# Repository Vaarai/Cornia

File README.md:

<h1 align="center">
 
</h1>

# Cornia keyboard

<h1 align="center">
 
</h1>

The Cornia keyboard is a split keyboard featuring : 
* 3x6 column strongly staggered keys and 3 thumb keys
* Hotswap sockets (Compatible with Kailh and Gateron)
* All 1u keys
* Same PCB for both hands (revesible)
* No diode to solder (No switch matrix)
* Per key adressable RGB leds (SK6812MINI-E)
* QMK Handedness pin (see [QMK documentation](https://github.com/qmk/qmk_firmware/blob/master/docs/config_options.md#setting-handedness))

### Why this name ?

Because it was inspired from the [Corne](https://github.com/foostan/crkbd/tree/main) keyboard, and `Cornia` came in mind.

### Table of contents

<!--ts-->
  * [Quick steps](#quick-steps)
  * [Hardware](#hardware)
    * [Bill of material](#bill-of-material)
    * [Compatible controllers](#compatible-controllers)
    * [PCB Design](#pcb-design-and-manufacturing)
    * [Keyboard assembling](#keyboard-assembling)
    * [Troubleshooting](#troubleshooting)
  * [Software](#software)
    * [Cornia not yet integrated in official QMK ?](#cornia-not-yet-integrated-in-official-qmk)
    * [Keymap](#keymap)
  * [Case](#case)
  * [Photos](#photos)
<!--te-->

# Quick steps

1. [Order the PCB](./doc/pcb_ordering.md)
2. [Print the case](https://www.printables.com/model/958200-case-for-cornia-v1-including-a-trackpad-version-40)
3. [Assemble/solder PCB](./doc/assembly_guide.md)
4. [Flash Cornia QMK](https://github.com/Vaarai/qmk_firmware/tree/cornia/keyboards/cornia)

# Hardware

### Bill of material

| Name | Count | Remarks |
|:-|:-|:-|
| PCB | 2 | [PCB Ordering guide](./doc/pcb_ordering.md) |
| OLED Display | 2 | |
| [RP2040 ProMicro](https://keeb.io/products/rp2040-pro-micro-usb-c-controller) | 2 | Alternative: Refer to [Compatible controllers](#compatible-controllers) |
| TRRS 3.5mm jack | 2 | Ref: PJ-320A |
| Reset switch | 2 | SMD 4x4mm |
| I²C Pull-up resistors | 2 | 0805 form-factor and any value between 2.2kΩ and 4.7kΩ |
| Handedness Pull-up/down resistor | 1 | 0805 form-factor and any value between 2.2kΩ and 4.7kΩ |
| Hotswap sockets | 42 | Compatible with Kailh and Gateron |
| Key switches | 42 | Only compatible with MX style |
| Keycaps | 42 | 1u size |
| TRRS (4 poles) cable | 1 | |
| USB cable | 1 | USB Micro or USB-C depending on the controller, avoid charge-only cables |
| Case | 2 | [Cornia v1 Printables](https://www.printables.com/model/958200-case-for-cornia-v1-including-a-trackpad-version-40) |

### Compatible controllers

| Reference | I²C OLED Display | Handedness pin | Other features |
|:-|:-:|:-:|:-:|
| [RP2040 Aliexpress](https://fr.aliexpress.com/item/1005005980167753.html) | $${\color{green}✓}$$ | $${\color{green}✓}$$ | $${\color{green}✓}$$ |
| [RP2040 keeb.io](https://keeb.io/products/rp2040-pro-micro-usb-c-controller) | $${\color{green}✓}$$ | $${\color{green}✓}$$ | $${\color{green}✓}$$ |
| [0xCB-Helios](https://github.com/0xCB-dev/0xCB-Helios) | $${\color{green}✓}$$ | $${\color{green}✓}$$ | $${\color{green}✓}$$ |
| [Elite-Pi](https://docs.keeb.io/elite-pi-guide) | $${\color{red}⨯}$$ | $${\color{red}⨯}$$ | $${\color{green}✓}$$ |
| [RP Micro](https://github.com/siderakb/rp-micro) | $${\color{red}⨯}$$ | $${\color{red}⨯}$$ | $${\color{green}✓}$$ |

### PCB design and manufacturing

Schematic and PCB views are available in `pdf/`:
- [Schematic](pdf/SCH.pdf)
- [PCB Top view](pdf/PCB_TOP.pdf)
- [PCB Bottom view](pdf/PCB_BOT.pdf)

To manufacture the Cornia PCB please follow the [PCB manufacturing guide](./doc/pcb_ordering.md)

In case you want to modify the PCB please take a look at the following:
- KiCad [project description](./PCB/README.md)
- Export bash script to ease the process, it is documented in [Manufacturing files export guide](./doc/manufacturing_files_export.md)

### Keyboard assembling

To solder and assemble the Cornia keyboard please follow the [Cornia assembly guide](./doc/assembly_guide.md)

### Troubleshooting

[Troubleshooting guide](./doc/troubleshooting_pcb.md)

# Software

Cornia keyboard firmware is based on QMK.

### Cornia not yet integrated in official QMK ?

If Cornia keyboard not yet integrated in [qmk_firmware](https://github.com/qmk/qmk_firmware) you can go to [Vaarai QMK fork](https://github.com/Vaarai/qmk_firmware/tree/cornia/keyboards/cornia) on and follow the readme.

### Keymap

- [Default QWERTY layout for Cornia keyboard](https://www.keyboard-layout-editor.com/#/gists/5af136790cefe4b35cdf02ca52c1fccc)
- [Fire layout for Cornia keyboard](https://www.keyboard-layout-editor.com/#/gists/a40345c92e1f3f326426ef890ebf4d1c) (Based on [Fire (Oxey)](https://bit.ly/layout-doc-v2) layout)

# Case

Case for Cornia v1 is available on [Cornia v1 Printables](https://www.printables.com/model/958200-case-for-cornia-v1-including-a-trackpad-version-40) from user Rikiki, optionally including a trackpad version (40mm) available for both halves.

Cornia keyboard is a project initiated by a post from `help-forum` on [QMK Discord](https://discord.gg/qmk).

User Rikiki requested in this post if someone could alter [crkbd](https://github.com/foostan/crkbd) PCB to match his requirements.

I (Vaarai) replied to this post and in 1 months we made 2 iterations of crkbd variant and it diverged from crkbd in a way that we started to make a new keyboard and 5 months later it lead to the Cornia.

Rikiki made all the mechanical parts and I designed the PCB then developed a QMK implementation.

# Photos

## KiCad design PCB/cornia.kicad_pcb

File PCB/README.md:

# Cornia KiCad project overview

This KiCad project is designed for the Cornia keyboard PCB

## KiCad files Descriptions

- __cornia.kicad_pro:__ This is the main project file for KiCad. It contains general information about the project, such as library paths, and links to schematic and PCB files.
- __cornia.sch:__ This file defines the circuit diagram and component connections.
- __cornia.kicad_pcb:__ This file contains the PCB layout, including component placement, routing, and layer definitions.
- __cornia.kicad_sym:__ This file defines the symbol for a custom component used in the schematics.
- __cornia.kicad_mod:__ This file defines the footprint for a custom component used in the PCB layout.
- __cornia.pdf:__ This file contains any relevant documentation or information about the project.

## Usage
- __Open the project:__ Launch KiCad and open __cornia.kicad_pro__ file.
- __View schematics:__ Open schematic file from the project view.
- __Inspect PCB layout:__ Open PCB layout file from the project view.
- __Modify as needed:__ Make any necessary changes to the schematics and/or PCB layout.
- __Generate Gerber files:__ If you're ready to manufacture the PCB, generate the Gerber files from the PCB layout.

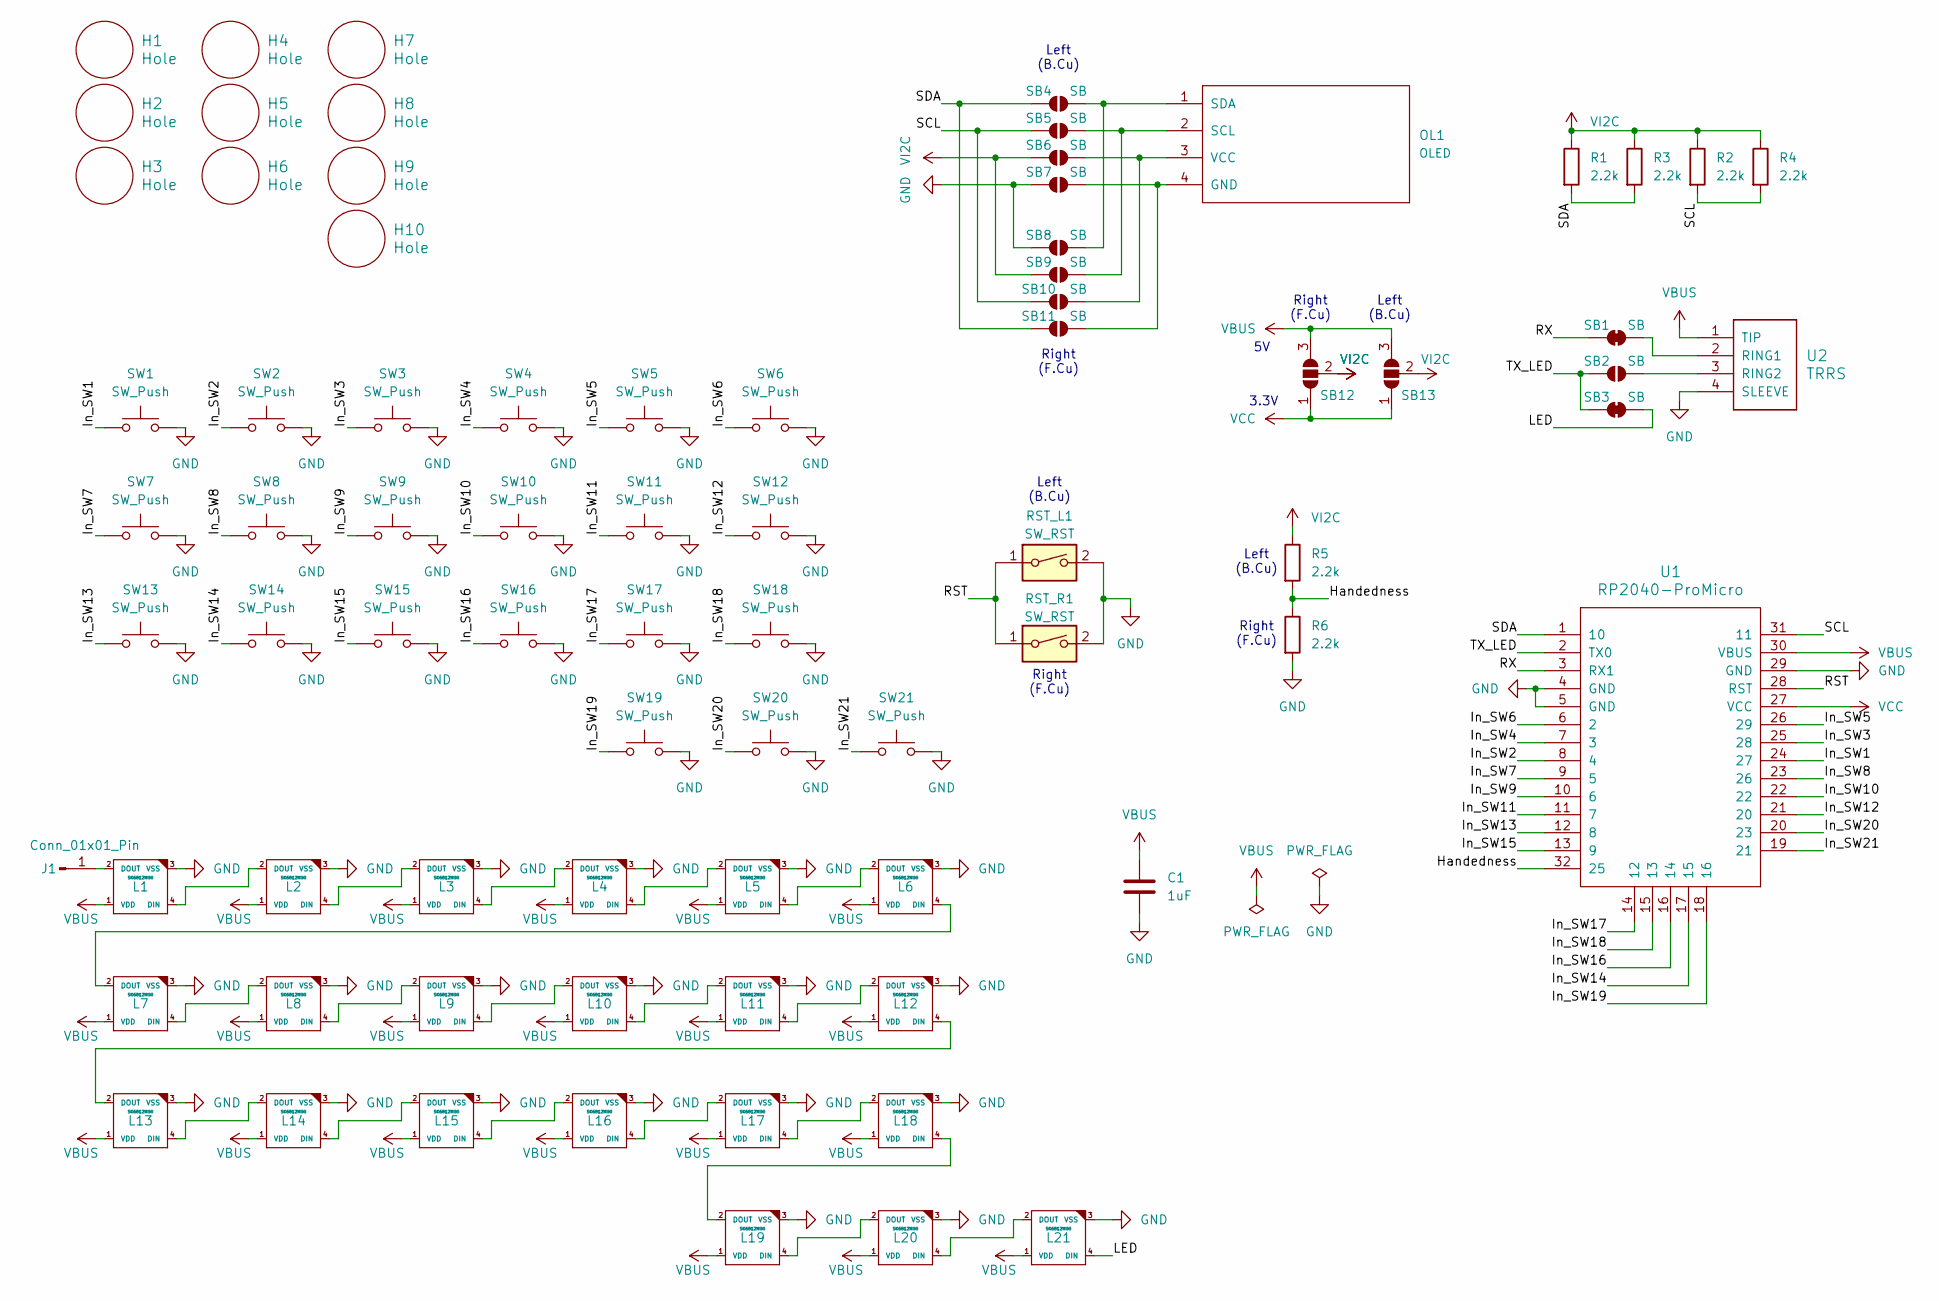
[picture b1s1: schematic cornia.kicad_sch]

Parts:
C1: 1uF; C_0805
H1, H2, H3, H4, H5, H6, H7, H8, H9, H10: Hole; MountingHole_2.2mm_M2_no_annular
J1: Conn_01x01_Pin; 1Pin
L1, L2, L3, L4, L5, L6, L7, L8, L9, L10, L11, L12, L13, L14, L15, L16, L17, L18, L19, L20, L21: SK6812MINI; YS-SK6812MINI-E
OL1: OLED
R1, R2, R3, R4, R5, R6: 2.2k; R_0805
RST_L1: SW_RST; SW_SMD_4x4mm
RST_R1: SW_RST; SW_SMD_4x4mm
SB1, SB3: SB; SolderJumper-2_Bridged
SB2: SB; SolderJumper-2_Open
SB4, SB5, SB6, SB7, SB8, SB9, SB10, SB11: SB; SolderJumper-2_Open_NoSilk
SB12, SB13: SolderJumper_3_Open; SolderJumper-3_I2C
SW1, SW2, SW3, SW4, SW5, SW6, SW7, SW8, SW9, SW10, SW11, SW12, SW13, SW14, SW15, SW16, SW17, SW18, SW19, SW20, SW21: SW_Push; keyswitch_cherrymx_hotswap_reversible_1u
U1: RP2040-ProMicro
U2: TRRS; TRRS_PJ-320A

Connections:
/Handedness: R5.2, R6.1, U1.32 (25)
/In_SW1: SW1.1, U1.24 (27)
/In_SW2: SW2.1, U1.8 (4)
/In_SW3: SW3.1, U1.25 (28)
/In_SW4: SW4.1, U1.7 (3)
/In_SW5: SW5.1, U1.26 (29)
/In_SW6: SW6.1, U1.6 (2)
/In_SW7: SW7.1, U1.9 (5)
/In_SW8: SW8.1, U1.23 (26)
/In_SW9: SW9.1, U1.10 (6)
/In_SW10: SW10.1, U1.22
/In_SW11: SW11.1, U1.11 (7)
/In_SW12: SW12.1, U1.21 (20)
/In_SW13: SW13.1, U1.12 (8)
/In_SW14: SW14.1, U1.17 (15)
/In_SW15: SW15.1, U1.13 (9)
/In_SW16: SW16.1, U1.16 (14)
/In_SW17: SW17.1, U1.14 (12)
/In_SW18: SW18.1, U1.15 (13)
/In_SW19: SW19.1, U1.18 (16)
/In_SW20: SW20.1, U1.20 (23)
/In_SW21: SW21.1, U1.19 (21)
/LED: L21.4 (DIN), SB3.2 (B)
/RST: RST_L1.1, RST_R1.1, U1.28 (RST)
/RX: SB1.1 (A), U1.3 (RX1)
/SCL: R2.2, R4.2, SB5.1 (A), SB10.1 (A), U1.31 (11)
/SDA: R1.2, R3.2, SB4.1 (A), SB11.1 (A), U1.1 (10)
/TX_LED: SB2.1 (A), SB3.1 (A), U1.2 (TX0)
GND: C1.2, L1.3 (VSS), L2.3 (VSS), L3.3 (VSS), L4.3 (VSS), L5.3 (VSS), L6.3 (VSS), L7.3 (VSS), L8.3 (VSS), L9.3 (VSS), L10.3 (VSS), L11.3 (VSS), L12.3 (VSS), L13.3 (VSS), L14.3 (VSS), L15.3 (VSS), L16.3 (VSS), L17.3 (VSS), L18.3 (VSS), L19.3 (VSS), L20.3 (VSS), L21.3 (VSS), R6.2, RST_L1.2, RST_R1.2, SB7.1 (A), SB8.1 (A), SW1.2, SW2.2, SW3.2, SW4.2, SW5.2, SW6.2, SW7.2, SW8.2, SW9.2, SW10.2, SW11.2, SW12.2, SW13.2, SW14.2, SW15.2, SW16.2, SW17.2, SW18.2, SW19.2, SW20.2, SW21.2, U1.4 (GND), U1.5 (GND), U1.29 (GND), U2.4 (SLEEVE)
unnamed: J1.1, L1.2 (DOUT)
unnamed: L1.4 (DIN), L2.2 (DOUT)
unnamed: L2.4 (DIN), L3.2 (DOUT)
unnamed: L3.4 (DIN), L4.2 (DOUT)
unnamed: L4.4 (DIN), L5.2 (DOUT)
unnamed: L5.4 (DIN), L6.2 (DOUT)
unnamed: L6.4 (DIN), L7.2 (DOUT)
unnamed: L7.4 (DIN), L8.2 (DOUT)
unnamed: L8.4 (DIN), L9.2 (DOUT)
unnamed: L10.4 (DIN), L11.2 (DOUT)
unnamed: L9.4 (DIN), L10.2 (DOUT)
unnamed: L11.4 (DIN), L12.2 (DOUT)
unnamed: L12.4 (DIN), L13.2 (DOUT)
unnamed: L13.4 (DIN), L14.2 (DOUT)
unnamed: L14.4 (DIN), L15.2 (DOUT)
unnamed: L15.4 (DIN), L16.2 (DOUT)
unnamed: L16.4 (DIN), L17.2 (DOUT)
unnamed: L17.4 (DIN), L18.2 (DOUT)
unnamed: L18.4 (DIN), L19.2 (DOUT)
unnamed: L19.4 (DIN), L20.2 (DOUT)
unnamed: L20.4 (DIN), L21.2 (DOUT)
unnamed: OL1.4 (GND), SB7.2 (B), SB11.2 (B)
unnamed: OL1.2 (SCL), SB5.2 (B), SB9.2 (B)
unnamed: OL1.1 (SDA), SB4.2 (B), SB8.2 (B)
unnamed: OL1.3 (VCC), SB6.2 (B), SB10.2 (B)
unnamed: SB1.2 (B), U2.2 (RING1)
unnamed: SB2.2 (B), U2.3 (RING2)
VBUS: C1.1, L1.1 (VDD), L2.1 (VDD), L3.1 (VDD), L4.1 (VDD), L5.1 (VDD), L6.1 (VDD), L7.1 (VDD), L8.1 (VDD), L9.1 (VDD), L10.1 (VDD), L11.1 (VDD), L12.1 (VDD), L13.1 (VDD), L14.1 (VDD), L15.1 (VDD), L16.1 (VDD), L17.1 (VDD), L18.1 (VDD), L19.1 (VDD), L20.1 (VDD), L21.1 (VDD), SB12.3 (B), SB13.3 (B), U1.30 (VBUS), U2.1 (TIP)
VCC: SB12.1 (A), SB13.1 (A), U1.27 (VCC)
VI2C: R1.1, R2.1, R3.1, R4.1, R5.1, SB6.1 (A), SB9.1 (A), SB12.2 (C), SB13.2 (C)

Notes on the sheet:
Right (F.Cu)
Left (B.Cu)
3.3V

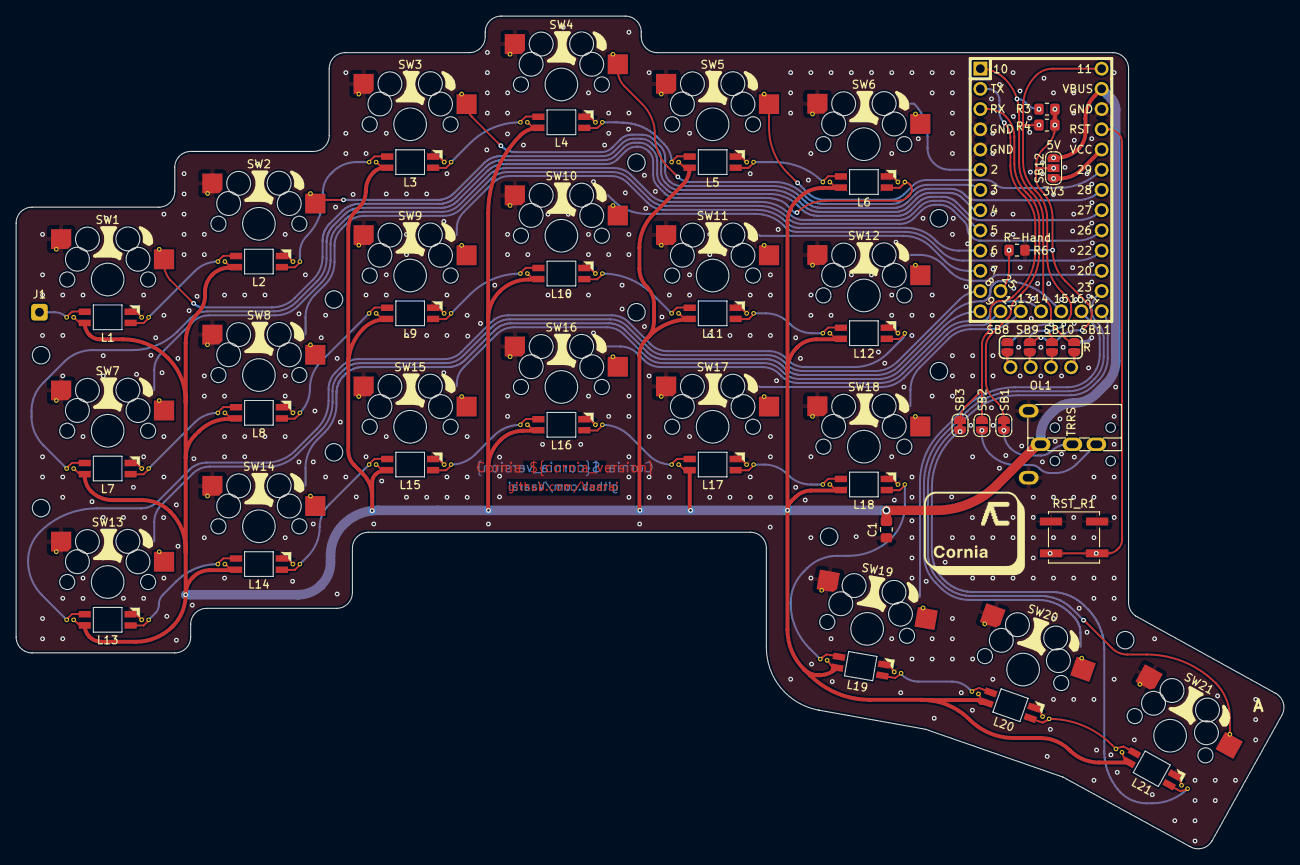
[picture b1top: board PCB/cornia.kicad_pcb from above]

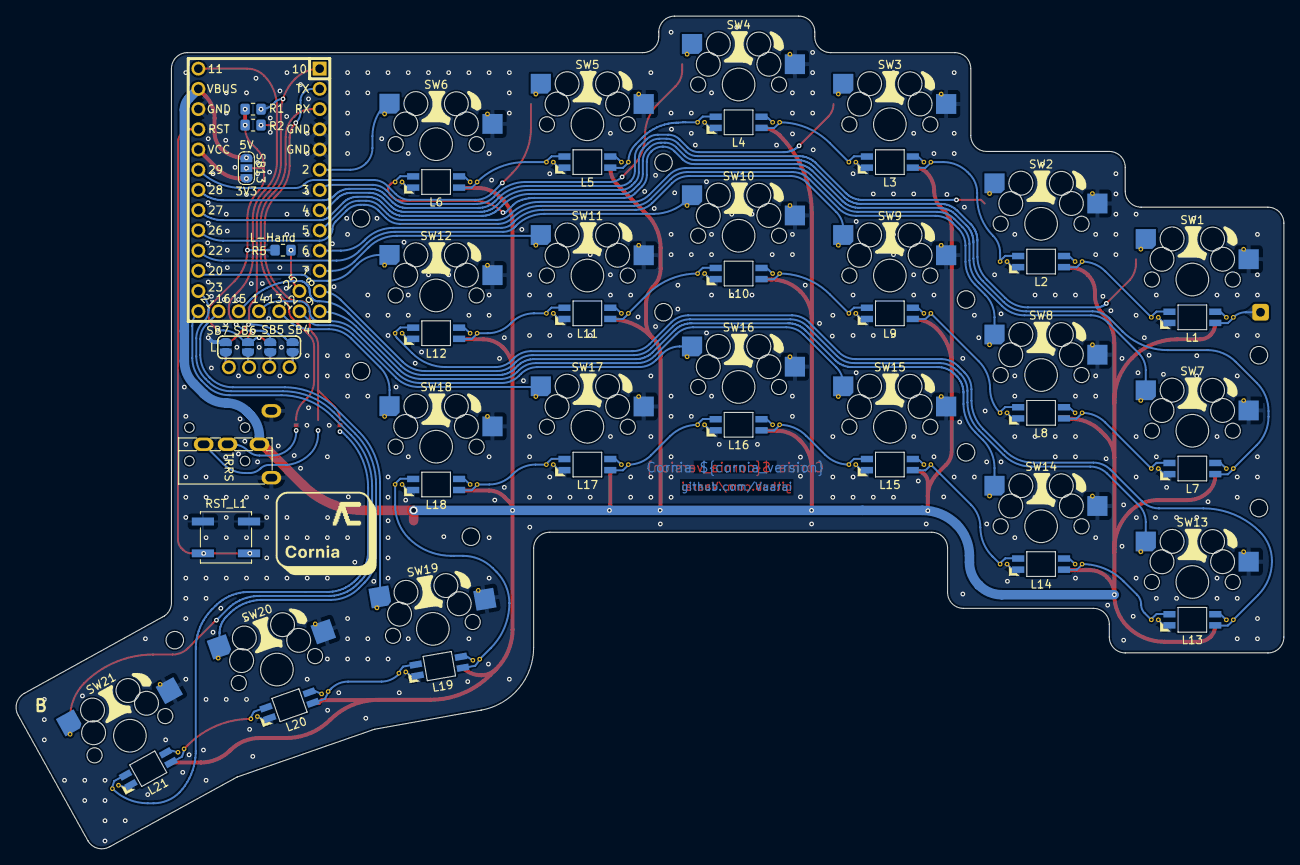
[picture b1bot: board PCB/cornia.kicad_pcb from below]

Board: 2 copper layers, 159.3 x 104.6 mm, 78 parts (9 on the bottom side), 59 nets.

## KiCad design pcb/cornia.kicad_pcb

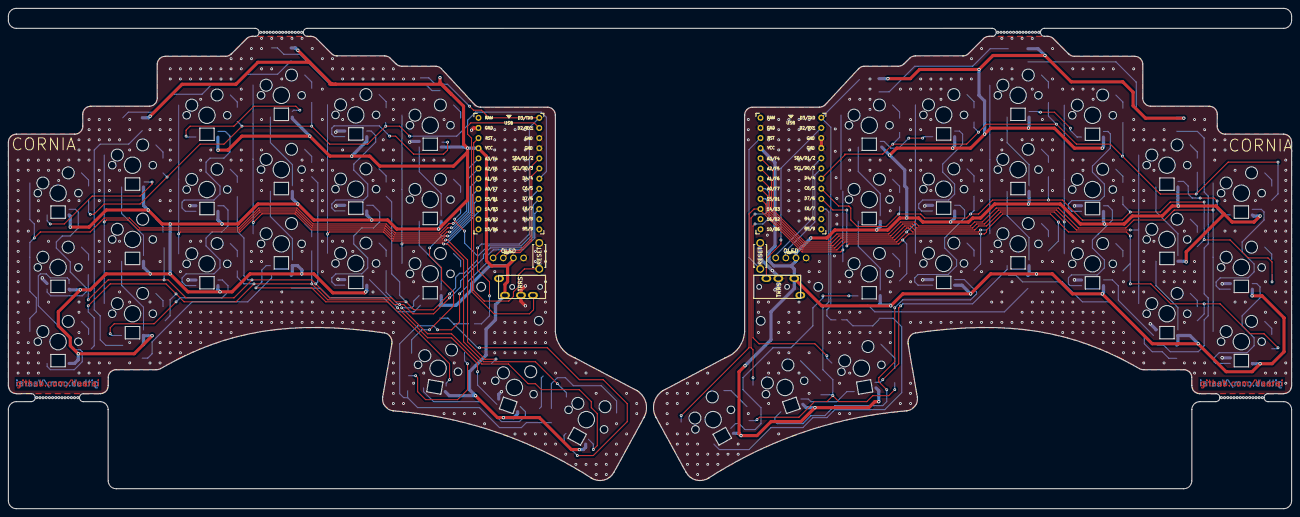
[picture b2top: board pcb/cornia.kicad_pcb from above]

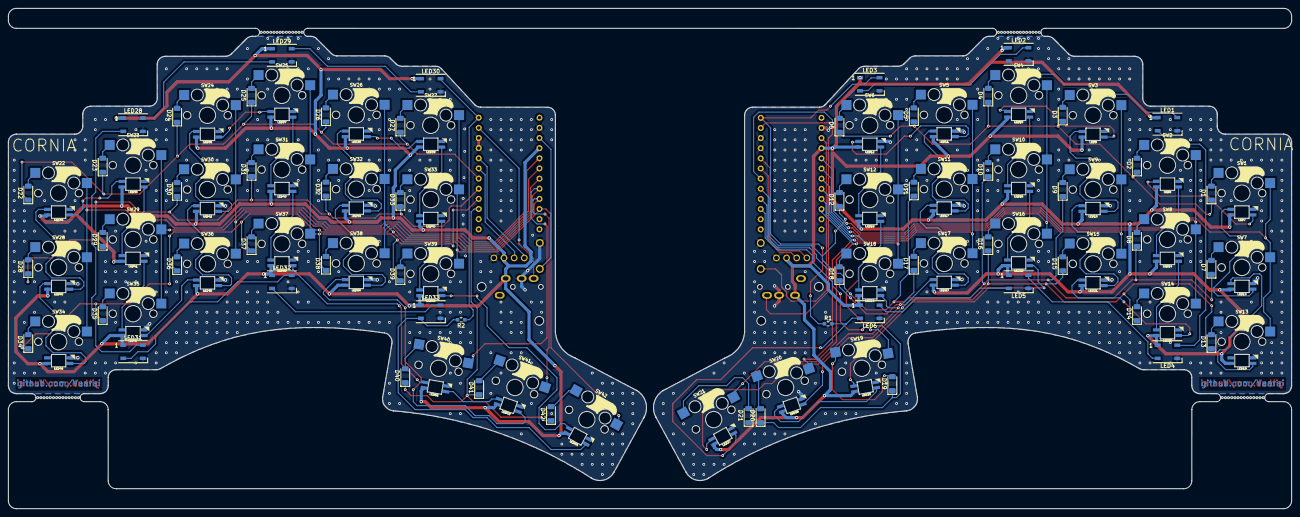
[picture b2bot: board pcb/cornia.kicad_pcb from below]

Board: 2 copper layers, 321.4 x 125.3 mm, 152 parts (142 on the bottom side), 128 nets.

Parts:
D1, D2, D3, D4, D5, D6, D7, D8, D9, D10, D11, D12, D13, D14, D15, D16, D17, D18, D19, D20, D21, D22, D23, D24, D25, D26, D27, D28, D29, D30, D31, D32, D33, D34, D35, D36, D37, D38, D39, D40, D41, D42: D; D_MiniMELF
J1, J3: MJ-4PP-9
J2, J4: OLED
LED1, LED2, LED3, LED4, LED5, LED6, LED28, LED29, LED30, LED31, LED32, LED33: WS2812B; LED_WS2812B_PLCC4_5.0x5.0mm_P3.2mm
LED7, LED8, LED9, LED10, LED11, LED12, LED13, LED14, LED15, LED16, LED17, LED18, LED19, LED20, LED21, LED22, LED23, LED24, LED25, LED26, LED27, LED34, LED35, LED36, LED37, LED38, LED39, LED40, LED41, LED42, LED43, LED44, LED45, LED46, LED47, LED48, LED49, LED50, LED51, LED52, LED53, LED54: YS-SK6812MINI-E
R1, R2: 0; R_0603_1608Metric_Pad0.98x0.95mm_HandSolder
RSW1, RSW2: SW_PUSH; ResetSW
Ref**: Val**; MountingHole_2.2mm_M2_ISO7380
Ref**#2, Ref**#3, Ref**#4: Val**; MountingHole_2.2mm_M2_ISO7380
SW1, SW2, SW3, SW4, SW5, SW6, SW7, SW8, SW9, SW10, SW11, SW12, SW13, SW14, SW15, SW16, SW17, SW18, SW19, SW20, SW21, SW22, SW23, SW24, SW25, SW26, SW27, SW28, SW29, SW30, SW31, SW32, SW33, SW34, SW35, SW36, SW37, SW38, SW39, SW40, SW41, SW42: SW_PUSH; keyswitch_cherrymx_hotswap_1u
U1, U2: ProMicro

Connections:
GND: J1.C, J2.4, LED1.3 (VSS), LED2.3 (VSS), LED3.3 (VSS), LED4.3 (VSS), LED5.3 (VSS), LED6.3 (VSS), LED7.3 (VSS), LED8.3 (VSS), LED9.3 (VSS), LED10.3 (VSS), LED11.3 (VSS), LED12.3 (VSS), LED13.3 (VSS), LED14.3 (VSS), LED15.3 (VSS), LED16.3 (VSS), LED17.3 (VSS), LED18.3 (VSS), LED19.3 (VSS), LED20.3 (VSS), LED21.3 (VSS), LED22.3 (VSS), LED23.3 (VSS), LED24.3 (VSS), LED25.3 (VSS), LED26.3 (VSS), LED27.3 (VSS), RSW1.2, U1.3 (GND), U1.4 (GND), U1.23 (GND)
GNDA: J3.C, J4.4, LED28.3 (VSS), LED29.3 (VSS), LED30.3 (VSS), LED31.3 (VSS), LED32.3 (VSS), LED33.3 (VSS), LED34.3 (VSS), LED35.3 (VSS), LED36.3 (VSS), LED37.3 (VSS), LED38.3 (VSS), LED39.3 (VSS), LED40.3 (VSS), LED41.3 (VSS), LED42.3 (VSS), LED43.3 (VSS), LED44.3 (VSS), LED45.3 (VSS), LED46.3 (VSS), LED47.3 (VSS), LED48.3 (VSS), LED49.3 (VSS), LED50.3 (VSS), LED51.3 (VSS), LED52.3 (VSS), LED53.3 (VSS), LED54.3 (VSS), RSW2.2, U2.3 (GND), U2.4 (GND), U2.23 (GND)
LED: LED3.4 (DIN), R1.1, U1.1 (TX0/D3)
LED_r: LED30.4 (DIN), R2.1, U2.1 (TX0/D3)
unnamed: D1.2 (A), SW1.2
unnamed: D2.2 (A), SW2.2
unnamed: D3.2 (A), SW3.2
unnamed: D4.2 (A), SW4.2
unnamed: D5.2 (A), SW5.2
unnamed: D6.2 (A), SW6.2
unnamed: D7.2 (A), SW7.2
unnamed: D8.2 (A), SW8.2
unnamed: D9.2 (A), SW9.2
unnamed: D10.2 (A), SW10.2
unnamed: D11.2 (A), SW11.2
unnamed: D12.2 (A), SW12.2
unnamed: D13.2 (A), SW13.2
unnamed: D14.2 (A), SW14.2
unnamed: D15.2 (A), SW15.2
unnamed: D16.2 (A), SW16.2
unnamed: D17.2 (A), SW17.2
unnamed: D18.2 (A), SW18.2
unnamed: D19.2 (A), SW19.2
unnamed: D20.2 (A), SW20.2
unnamed: D21.2 (A), SW21.2
unnamed: D22.2 (A), SW22.2
unnamed: D23.2 (A), SW23.2
unnamed: D24.2 (A), SW24.2
unnamed: D25.2 (A), SW25.2
unnamed: D26.2 (A), SW26.2
unnamed: D27.2 (A), SW27.2
unnamed: D28.2 (A), SW28.2
unnamed: D29.2 (A), SW29.2
unnamed: D30.2 (A), SW30.2
unnamed: D31.2 (A), SW31.2
unnamed: D32.2 (A), SW32.2
unnamed: D33.2 (A), SW33.2
unnamed: D34.2 (A), SW34.2
unnamed: D35.2 (A), SW35.2
unnamed: D36.2 (A), SW36.2
unnamed: D37.2 (A), SW37.2
unnamed: D38.2 (A), SW38.2
unnamed: D39.2 (A), SW39.2
unnamed: D40.2 (A), SW40.2
unnamed: D41.2 (A), SW41.2
unnamed: D42.2 (A), SW42.2
unnamed: LED1.4 (DIN), LED2.2 (DOUT)
unnamed: LED1.2 (DOUT), LED4.4 (DIN)
unnamed: LED2.4 (DIN), LED3.2 (DOUT)
unnamed: LED4.2 (DOUT), LED5.4 (DIN)
unnamed: LED5.2 (DOUT), LED6.4 (DIN)
unnamed: LED7.4 (DIN), LED8.2 (DOUT)
unnamed: LED10.4 (DIN), LED16.2 (DOUT)
unnamed: LED9.4 (DIN), LED10.2 (DOUT)
unnamed: LED11.4 (DIN), LED12.2 (DOUT)
unnamed: LED11.2 (DOUT), LED17.4 (DIN)
unnamed: LED12.4 (DIN), LED18.2 (DOUT)
unnamed: LED7.2 (DOUT), LED13.4 (DIN)
unnamed: LED13.2 (DOUT), LED19.4 (DIN)
unnamed: LED14.4 (DIN), LED20.2 (DOUT)
unnamed: LED8.4 (DIN), LED14.2 (DOUT)
unnamed: LED9.2 (DOUT), LED15.4 (DIN)
unnamed: LED15.2 (DOUT), LED21.4 (DIN)
unnamed: LED16.4 (DIN), LED22.2 (DOUT)
unnamed: LED17.2 (DOUT), LED23.4 (DIN)
unnamed: LED18.4 (DIN), LED24.2 (DOUT)
unnamed: LED20.4 (DIN), LED21.2 (DOUT)
unnamed: LED22.4 (DIN), LED25.2 (DOUT)
unnamed: LED23.2 (DOUT), LED26.4 (DIN)
unnamed: LED24.4 (DIN), LED27.2 (DOUT)
unnamed: LED25.4 (DIN), LED26.2 (DOUT)
unnamed: LED6.2 (DOUT), LED27.4 (DIN), R1.2
unnamed: LED28.4 (DIN), LED29.2 (DOUT)
unnamed: LED28.2 (DOUT), LED31.4 (DIN)
unnamed: LED29.4 (DIN), LED30.2 (DOUT)
unnamed: LED31.2 (DOUT), LED32.4 (DIN)
unnamed: LED32.2 (DOUT), LED33.4 (DIN)
unnamed: LED33.2 (DOUT), LED54.4 (DIN), R2.2
unnamed: LED34.4 (DIN), LED35.2 (DOUT)
unnamed: LED34.2 (DOUT), LED40.4 (DIN)
unnamed: LED35.4 (DIN), LED41.2 (DOUT)
unnamed: LED36.4 (DIN), LED37.2 (DOUT)
unnamed: LED36.2 (DOUT), LED42.4 (DIN)
unnamed: LED37.4 (DIN), LED43.2 (DOUT)
unnamed: LED38.4 (DIN), LED39.2 (DOUT)
unnamed: LED38.2 (DOUT), LED44.4 (DIN)
unnamed: LED39.4 (DIN), LED45.2 (DOUT)
unnamed: LED40.2 (DOUT), LED46.4 (DIN)
unnamed: LED41.4 (DIN), LED47.2 (DOUT)
unnamed: LED42.2 (DOUT), LED48.4 (DIN)
unnamed: LED43.4 (DIN), LED49.2 (DOUT)
unnamed: LED44.2 (DOUT), LED50.4 (DIN)
unnamed: LED45.4 (DIN), LED51.2 (DOUT)
unnamed: LED47.4 (DIN), LED48.2 (DOUT)
unnamed: LED49.4 (DIN), LED52.2 (DOUT)
unnamed: LED50.2 (DOUT), LED53.4 (DIN)
unnamed: LED51.4 (DIN), LED54.2 (DOUT)
unnamed: LED52.4 (DIN), LED53.2 (DOUT)
SCL: J2.2, U1.6 (3/D0/SCL)
SCL_r: J4.2, U2.6 (3/D0/SCL)
SDA: J2.1, U1.5 (2/D1/SDA)
SDA_r: J4.1, U2.5 (2/D1/SDA)
VCC: J1.D, J2.3, LED1.1 (VDD), LED2.1 (VDD), LED3.1 (VDD), LED4.1 (VDD), LED5.1 (VDD), LED6.1 (VDD), LED7.1 (VDD), LED8.1 (VDD), LED9.1 (VDD), LED10.1 (VDD), LED11.1 (VDD), LED12.1 (VDD), LED13.1 (VDD), LED14.1 (VDD), LED15.1 (VDD), LED16.1 (VDD), LED17.1 (VDD), LED18.1 (VDD), LED19.1 (VDD), LED20.1 (VDD), LED21.1 (VDD), LED22.1 (VDD), LED23.1 (VDD), LED24.1 (VDD), LED25.1 (VDD), LED26.1 (VDD), LED27.1 (VDD), U1.21 (VCC)
VDD: J3.D, J4.3, LED28.1 (VDD), LED29.1 (VDD), LED30.1 (VDD), LED31.1 (VDD), LED32.1 (VDD), LED33.1 (VDD), LED34.1 (VDD), LED35.1 (VDD), LED36.1 (VDD), LED37.1 (VDD), LED38.1 (VDD), LED39.1 (VDD), LED40.1 (VDD), LED41.1 (VDD), LED42.1 (VDD), LED43.1 (VDD), LED44.1 (VDD), LED45.1 (VDD), LED46.1 (VDD), LED47.1 (VDD), LED48.1 (VDD), LED49.1 (VDD), LED50.1 (VDD), LED51.1 (VDD), LED52.1 (VDD), LED53.1 (VDD), LED54.1 (VDD), U2.21 (VCC)
col0: SW1.1, SW7.1, SW13.1, U1.20 (F4/A3)
col0_r: SW22.1, SW28.1, SW34.1, U2.20 (F4/A3)
col1: SW2.1, SW8.1, SW14.1, U1.19 (F5/A2)
col1_r: SW23.1, SW29.1, SW35.1, U2.19 (F5/A2)
col2: SW3.1, SW9.1, SW15.1, U1.18 (F6/A1)
col2_r: SW24.1, SW30.1, SW36.1, U2.18 (F6/A1)
col3: SW4.1, SW10.1, SW16.1, SW19.1, U1.17 (F7/A0)
col3_r: SW25.1, SW31.1, SW37.1, SW40.1, U2.17 (F7/A0)
col4: SW5.1, SW11.1, SW17.1, SW20.1, U1.16 (B1/15)
col4_r: SW26.1, SW32.1, SW38.1, SW41.1, U2.16 (B1/15)
col5: SW6.1, SW12.1, SW18.1, SW21.1, U1.15 (B3/14)
col5_r: SW27.1, SW33.1, SW39.1, SW42.1, U2.15 (B3/14)
data: J1.B, U1.2 (RX1/D2)
data_r: J3.B, U2.2 (RX1/D2)
reset: RSW1.1, U1.22 (RST)
reset_r: RSW2.1, U2.22 (RST)
row0: D1.1 (K), D2.1 (K), D3.1 (K), D4.1 (K), D5.1 (K), D6.1 (K), U1.7 (4/D4)
row0_r: D22.1 (K), D23.1 (K), D24.1 (K), D25.1 (K), D26.1 (K), D27.1 (K), U2.7 (4/D4)
row1: D7.1 (K), D8.1 (K), D9.1 (K), D10.1 (K), D11.1 (K), D12.1 (K), U1.8 (5/C6)
row1_r: D28.1 (K), D29.1 (K), D30.1 (K), D31.1 (K), D32.1 (K), D33.1 (K), U2.8 (5/C6)
row2: D13.1 (K), D14.1 (K), D15.1 (K), D16.1 (K), D17.1 (K), D18.1 (K), U1.9 (6/D7)
row2_r: D34.1 (K), D35.1 (K), D36.1 (K), D37.1 (K), D38.1 (K), D39.1 (K), U2.9 (6/D7)
row3: D19.1 (K), D20.1 (K), D21.1 (K), U1.10 (7/E6)
row3_r: D40.1 (K), D41.1 (K), D42.1 (K), U2.10 (7/E6)

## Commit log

2024-04-23 [PCB] Add mounting hole User.Eco2 layer for dxf export
2024-05-18 [PCB] Remove mounting Hole and give space in front of USB connector
2024-05-28 First push V1
2024-05-30 Finish routing & add gerber/case export in CLI
2024-05-30 [Img/Doc] Update doc & Add 3D view
2024-05-31 Finish PCB, add fab output, update doc
2024-06-04 [Doc/Img] Add Helios as compatible controller & add alt banner
2024-06-04 [PCB] Add handedness pin
2024-06-08 [Doc&Tool] Update documentation & Add export script
2024-06-08 [PCB] Rework OLED SBx & Add last led DOUT TP
2024-06-10 [Doc] Update manufacturing docuentation
2024-06-10 [Tools] Update export script and add .step export
2024-06-12 [Doc] Add troubleshooting guide
2024-06-13 [PCB] Move 2mm left MCU/TRRS/RST
2024-06-19 [PCB/Footprint] Remove 5mm mounting hole + update RP2040 & RST 3D
2024-06-19 [Output] Update
2024-07-06 [Readme/Images] Add new logo
2024-07-06 [PCB/Symbol] Add 10x 2.2mm holes + Add new logo
2024-07-06 [Images] Update banner
2024-07-06 [PCB/Output] Increase Oled pads diameter + update output
2024-07-06 [PCB/Output] Add teardrop + update output
2024-07-08 [PCB/Footprint] Increase Oled pads size + Cut PCB angle near USB
2024-07-08 [Output] Generate fab output
2024-08-29 [Doc] Add assembly guide draft
2024-08-30 [FW] Add v0.6 FW to keep it somewhere
2024-08-30 [FW] Add FW v1 (not tested)
2024-08-31 [IMG] Add Fire KLE keymap .png
2024-09-01 [FW] Differentiate v1 & v0.6 by adding two folders
2024-09-02 [FW] Add v0.6 RP2040 alongside v0.6 ProMicro
2024-09-02 [Doc] Fix uC placement instruction
2024-09-02 [PCB] Fix RGB Led pin assignment mistake
2024-09-02 [PCB DRC] Edit 'vias' props in switch and led footprint to avoid SMD/THT DRC confusion
2024-09-02 [PCB DRC] Enable 'hole to hole' DRC and fix all issues
2024-09-02 [PCB] Multiple fix based on v1RC2 board bring-up
    - Reduce RST thermal relief width
    - Update SB silkscreen
    - Update TRRS silkscreen
2024-09-02 [PCB] Swap TX RX pins
2024-09-18 [FW] Harmonize and symplify config files (.h .mk .json)
2024-09-18 [PCB] Swap RST_L1 & RST_R1 to match their respective sides
2024-09-18 [Doc] Add pictures to assembly guide for SMDs
2024-09-18 [PCB] Fix handedness pin voltage (fixed to 3v3)
2024-09-18 [FW] Finish v1 integration with OLED & Cirque
2024-09-20 [FW] Improve Cirque & Split source files
2024-09-22 [FW] Add trackpad scrolling
2024-09-24 [Project] Change license
2024-09-24 [Project] Add Contributing guidelines
2024-09-24 [Doc] Add PCB readme
2024-09-24 [FW] Add shift_capsword tap dance
2024-09-25 [FW] Remove v0.6-promicro & tools folders
2024-09-25 [FW] Replace default layout by QWERTY
2024-09-25 [FW] Update firmware readme
2024-09-25 [FW] Add 'v1_no_led'
2024-09-25 [Doc] Update Software section
2024-09-26 [Doc] Add build image
2024-09-27 [Doc] Add case section and link
2024-09-27 [Doc] Redirect to Vaarai QMK fork
2024-09-27 [Doc] Add `Quick steps` section
